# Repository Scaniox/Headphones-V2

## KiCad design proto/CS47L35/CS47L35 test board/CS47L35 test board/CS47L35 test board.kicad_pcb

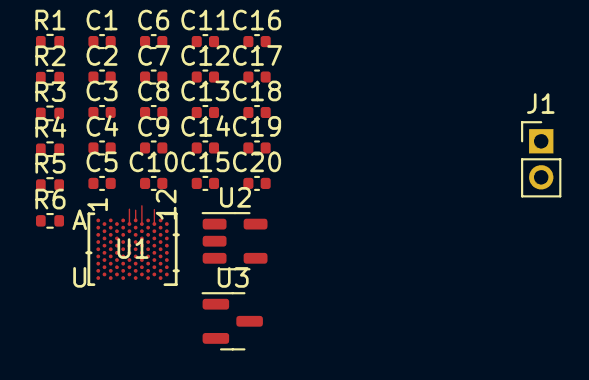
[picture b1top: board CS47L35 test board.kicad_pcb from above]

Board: 2 copper layers, 30 parts (0 on the bottom side), 27 nets.

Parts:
C1, C2, C3, C6, C7, C11, C12, C13, C14, C15, C20: 4.7uf; C_0402_1005Metric
C4, C8, C10: 2.2uf; C_0402_1005Metric
C5, C18, C19: 1uf; C_0402_1005Metric
C9: 470nf; C_0402_1005Metric
C16, C17: 100nf; C_0402_1005Metric
J1: Conn_01x02; PinHeader_1x02_P2.00mm_Vertical
R1, R2, R4, R5: 10k; R_0402_1005Metric
R3: 100k; R_0402_1005Metric
R6: 4.7; R_0402_1005Metric
U1: CS47L35-CWZR‎; BGA_CS47L35-CWZR_CIR
U2: AP2127K-1.8TRG1; SOT-23-5
U3: MCP1700x-300xxTT; SOT-23

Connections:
+1V2: C1.2, C2.1, R6.1, U1.C7 (CPVDD2), U1.U7 (DCVDD), U3.2 (VO)
+1V8: C20.1, R1.1, R2.1, R3.1, R4.1, R5.1, U1.A5 (CPVDD1), U2.5 (VOUT), U3.3 (VI)
+3V3: C3.2, C6.2, C16.1, C17.1, U1.R1 (SPKVDD), U1.U1 (SPKVDD), U1.U5 (DBVDD2), U1.U11 (DBVDD1), U2.1 (VIN), U2.3 (EN)
/CS47L35 core/CIF2SCLK: R2.2, U1.P12 (CIF2SCLK)
/CS47L35 core/CIF2SDA: R1.2, U1.N11 (CIF2SDA)
/CS47L35 core/HP_OUT_L: U1.A11 (HPOUTL), U1.C11 (HPDETL)
/CS47L35 core/HP_OUT_R: U1.B10 (HPOUTR), U1.B12 (HPDETR)
/CS47L35 core/JTAG_TDI: U1.K8 (TMS), U1.N7 (TDI)
/CS47L35 core/MIC_VDD: C7.1, U1.B4 (MICVDD)
/~IRQ: R3.2, U1.J9 (*IRQ)
GND: C1.1, C2.2, C3.1, C4.1, C5.1, C6.1, C7.2, C11.2, C12.2, C13.2, C14.2, C15.2, C16.2, C17.2, C18.1, C19.1, C20.2, U1.B6 (CPGND), U1.E9 (AGND2), U1.G11 (AGND2), U1.H12 (SUBGND), U1.J11 (DGND), U1.L1 (AGND1), U1.N1 (SUBGND), U1.R3 (SPKGNDN), U1.T4 (DGND), U1.U3 (SPKGNDP), U1.U9 (DGND), U2.2 (GND), U3.1 (GND)
unnamed: R4.2, U1.T8 (MIF1SCLK/GPIO16)
unnamed: R5.2, U1.P8 (MIF1SDA/GPIO07)
unnamed: C18.2, C19.2, U1.F12 (AVDD2), U1.K2 (AVDD1)
unnamed: C8.1, U1.E5 (CP1C1A)
unnamed: C8.2, U1.D6 (CP1C1B)
unnamed: C9.1, U1.C5 (CP1C2A)
unnamed: C9.2, U1.B8 (CP1C2B)
unnamed: C11.1, U1.E7 (CP1VOUT1N)
unnamed: C14.1, U1.F8 (CP1VOUT1P)
unnamed: C12.1, U1.A7 (CP1VOUT2N)
unnamed: C15.1, U1.D8 (CP1VOUT2P)
unnamed: C10.1, U1.G7 (CP2CA)
unnamed: C10.2, U1.G5 (CP2CB)
unnamed: C13.1, U1.F4 (CP2VOUT)
unnamed: C5.2, R6.2, U1.K12 (FLLVDD)
unnamed: C4.2, U1.J1 (VREFC)

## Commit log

2023-12-05 training workspace not building - mtb shared issue, starting workspace 2
2023-12-07 debug on the cyw20719 works !
2024-02-03 about to try debug audio sink example
2024-02-03 connects with codec init bamboozled
2024-02-04 cs47l35 rearanged a bit
2024-03-17 trying to build on btsdk basic example
2024-03-19 now appears and gets some events when i try to connect
2024-03-19 ignore goofy files
2024-03-19 responce and request seem confused
2024-03-19 fixed weird managment event enum number with a random define WICED_X
